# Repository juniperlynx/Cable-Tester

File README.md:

# Cable-Tester
This is a replacement PCB and software for a cheap commercial cable tester usually sold as the HL-486 (though there are other model numbers, mine is ST-M810).
It improves on the original design by adding beefier drive circuitry and a proper voltage regulator for the microcontroller.

Schematics and PCB layouts are available for both ends. The current revision of the Gerbers is untested but only contains slight variations from the most recently ordered version. Complete BOMs for both the master and remote ends are now available for both ends along with Digikey shoping carts in .csv format. I haven't been able to find a source for the multi-LED standoffs used to space the strand indicator LEDs so I've modeled a part in OpenSCAD. The OpenSCAD source and a rendered .stl file are available but untested at this time.

The original Kicad design files are in "Kicad Files/" and the software source code in "Software/".
If you'd like to build your own use the Gerber files in "Gerbers/" and the BOMs in "BOM/" along with the standoff model in "3D Parts/STL"

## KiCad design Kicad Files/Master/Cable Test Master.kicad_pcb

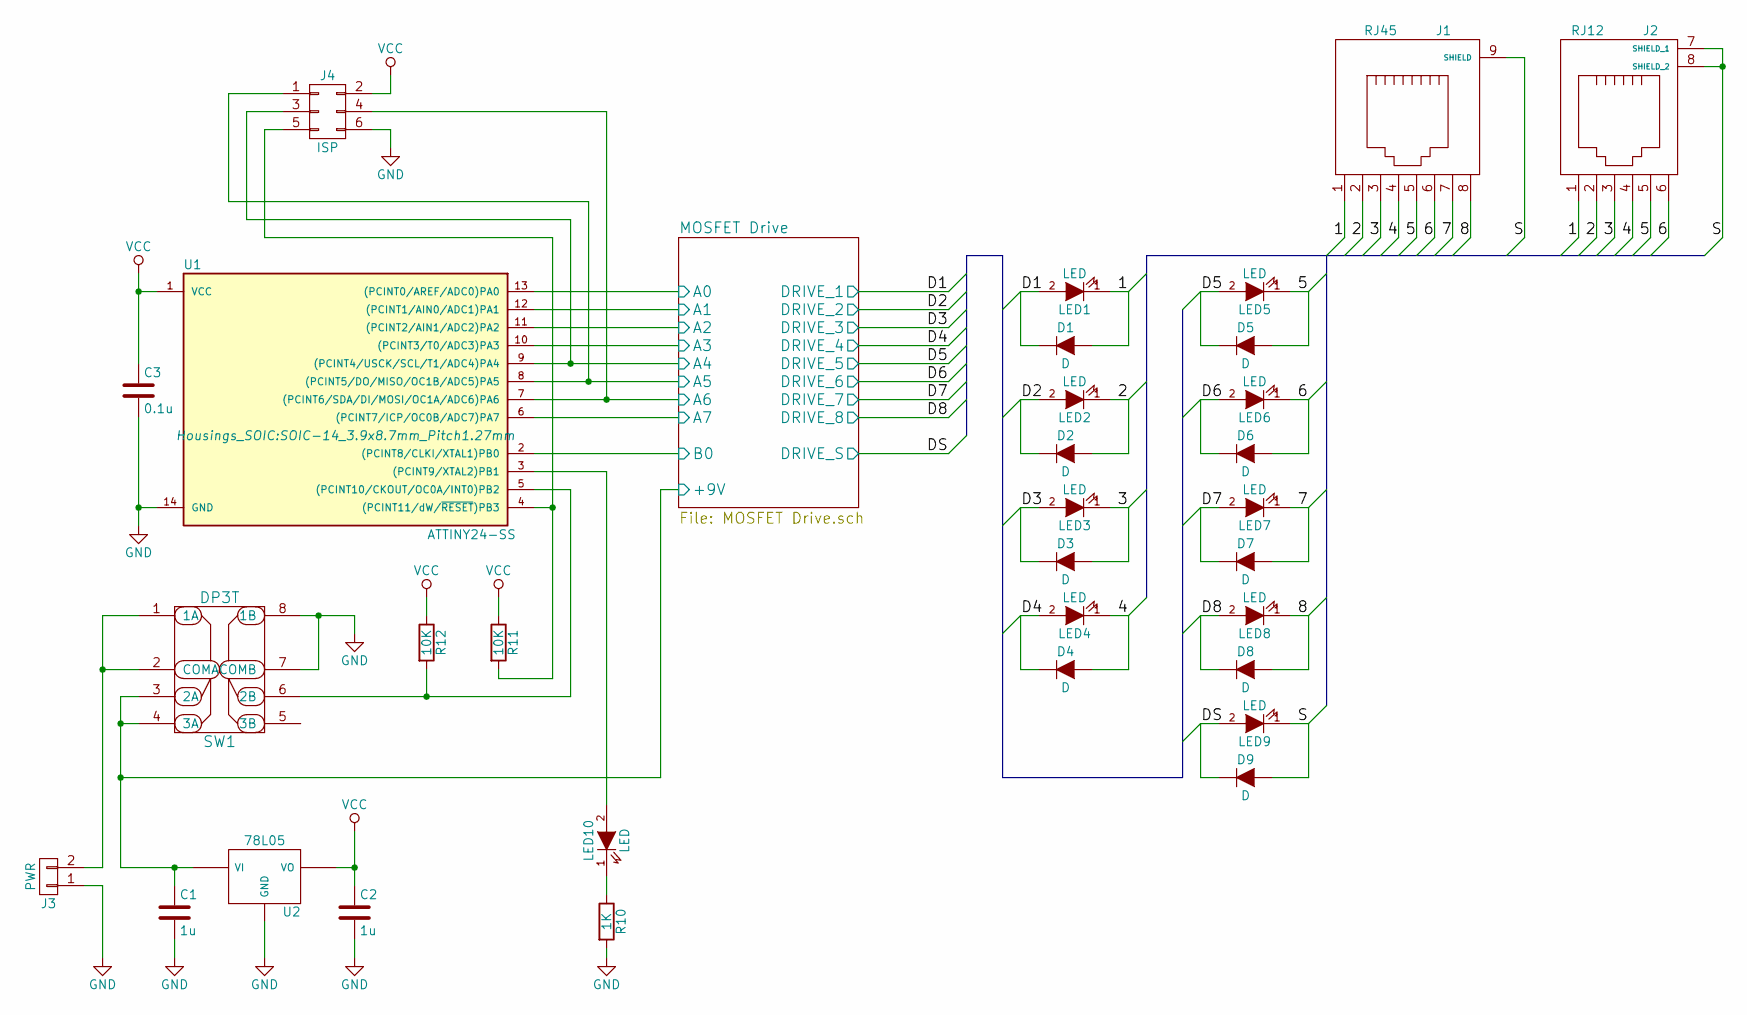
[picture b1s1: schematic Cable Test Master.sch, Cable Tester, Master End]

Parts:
C1, C2: 1u; C_0805_HandSoldering
C3: 0.1u; C_0805_HandSoldering
D1, D2, D3, D4, D5, D6, D7, D8, D9: D; SOD-123
J1: RJ45; RJ45_SHLD
J2: RJ12; RJ12_SHLD
J3: PWR; Pin_Header_Straight_1x02
J4: ISP; Pin_Header_Straight_2x03
LED1, LED2, LED3, LED4, LED5, LED6, LED7, LED8, LED9, LED10: LED; LED-3MM
R10: 1K; R_0805_HandSoldering
R11, R12: 10K; R_0805_HandSoldering
SW1: DP3T; SW_DP3T_SLIDE
U1: ATTINY24-SS; SOIC-14_3.9x8.7mm_Pitch1.27mm
U2: 78L05; 78L05_SOIC

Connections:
/1: D1.2 (A), J1.1, J2.1, LED1.1 (K)
/2: D2.2 (A), J1.2, J2.2, LED2.1 (K)
/3: D3.2 (A), J1.3, J2.3, LED3.1 (K)
/4: D4.2 (A), J1.4, J2.4, LED4.1 (K)
/5: D5.2 (A), J1.5, J2.5, LED5.1 (K)
/6: D6.2 (A), J1.6, J2.6, LED6.1 (K)
/7: D7.2 (A), J1.7, LED7.1 (K)
/8: D8.2 (A), J1.8, LED8.1 (K)
/MOSFET Drive/+9V: C1.1, SW1.3 (2A), SW1.4 (3A), U2.VI; also elsewhere on the board
/MOSFET Drive/A0: U1.13 ((PCINT0/AREF/ADC0)PA0); also elsewhere on the board
/MOSFET Drive/A1: U1.12 ((PCINT1/AIN0/ADC1)PA1); also elsewhere on the board
/MOSFET Drive/A2: U1.11 ((PCINT2/AIN1/ADC2)PA2); also elsewhere on the board
/MOSFET Drive/A3: U1.10 ((PCINT3/T0/ADC3)PA3); also elsewhere on the board
/MOSFET Drive/A4: J4.3, U1.9 ((PCINT4/USCK/SCL/T1/ADC4)PA4); also elsewhere on the board
/MOSFET Drive/A5: J4.1, U1.8 ((PCINT5/DO/MISO/OC1B/ADC5)PA5); also elsewhere on the board
/MOSFET Drive/A6: J4.4, U1.7 ((PCINT6/SDA/DI/MOSI/OC1A/ADC6)PA6); also elsewhere on the board
/MOSFET Drive/A7: U1.6 ((PCINT7/ICP/OC0B/ADC7)PA7); also elsewhere on the board
/MOSFET Drive/B0: U1.2 ((PCINT8/CLKI/XTAL1)PB0); also elsewhere on the board
/MOSFET Drive/DRIVE_1: D1.1 (K), LED1.2 (A); also elsewhere on the board
/MOSFET Drive/DRIVE_2: D2.1 (K), LED2.2 (A); also elsewhere on the board
/MOSFET Drive/DRIVE_3: D3.1 (K), LED3.2 (A); also elsewhere on the board
/MOSFET Drive/DRIVE_4: D4.1 (K), LED4.2 (A); also elsewhere on the board
/MOSFET Drive/DRIVE_5: D5.1 (K), LED5.2 (A); also elsewhere on the board
/MOSFET Drive/DRIVE_6: D6.1 (K), LED6.2 (A); also elsewhere on the board
/MOSFET Drive/DRIVE_7: D7.1 (K), LED7.2 (A); also elsewhere on the board
/MOSFET Drive/DRIVE_8: D8.1 (K), LED8.2 (A); also elsewhere on the board
/MOSFET Drive/DRIVE_S: D9.1 (K), LED9.2 (A); also elsewhere on the board
/S: D9.2 (A), J1.9 (SHIELD), J2.7 (SHIELD_1), J2.8 (SHIELD_2), LED9.1 (K)
GND: C1.2, C2.2, C3.2, J3.1, J4.6, R10.2, SW1.7 (COMB), SW1.8 (1B), U1.14 (GND), U2.GND; also elsewhere on the board
unnamed: J3.2, SW1.1 (1A), SW1.2 (COMA)
unnamed: J4.5, R11.2, U1.4 ((PCINT11/dW/~RESET~)PB3)
unnamed: LED10.1 (K), R10.1
unnamed: LED10.2 (A), U1.3 ((PCINT9/XTAL2)PB1)
unnamed: R12.2, SW1.6 (2B), U1.5 ((PCINT10/CKOUT/OC0A/INT0)PB2)
VCC: C2.1, C3.1, J4.2, R11.1, R12.1, U1.1 (VCC), U2.VO

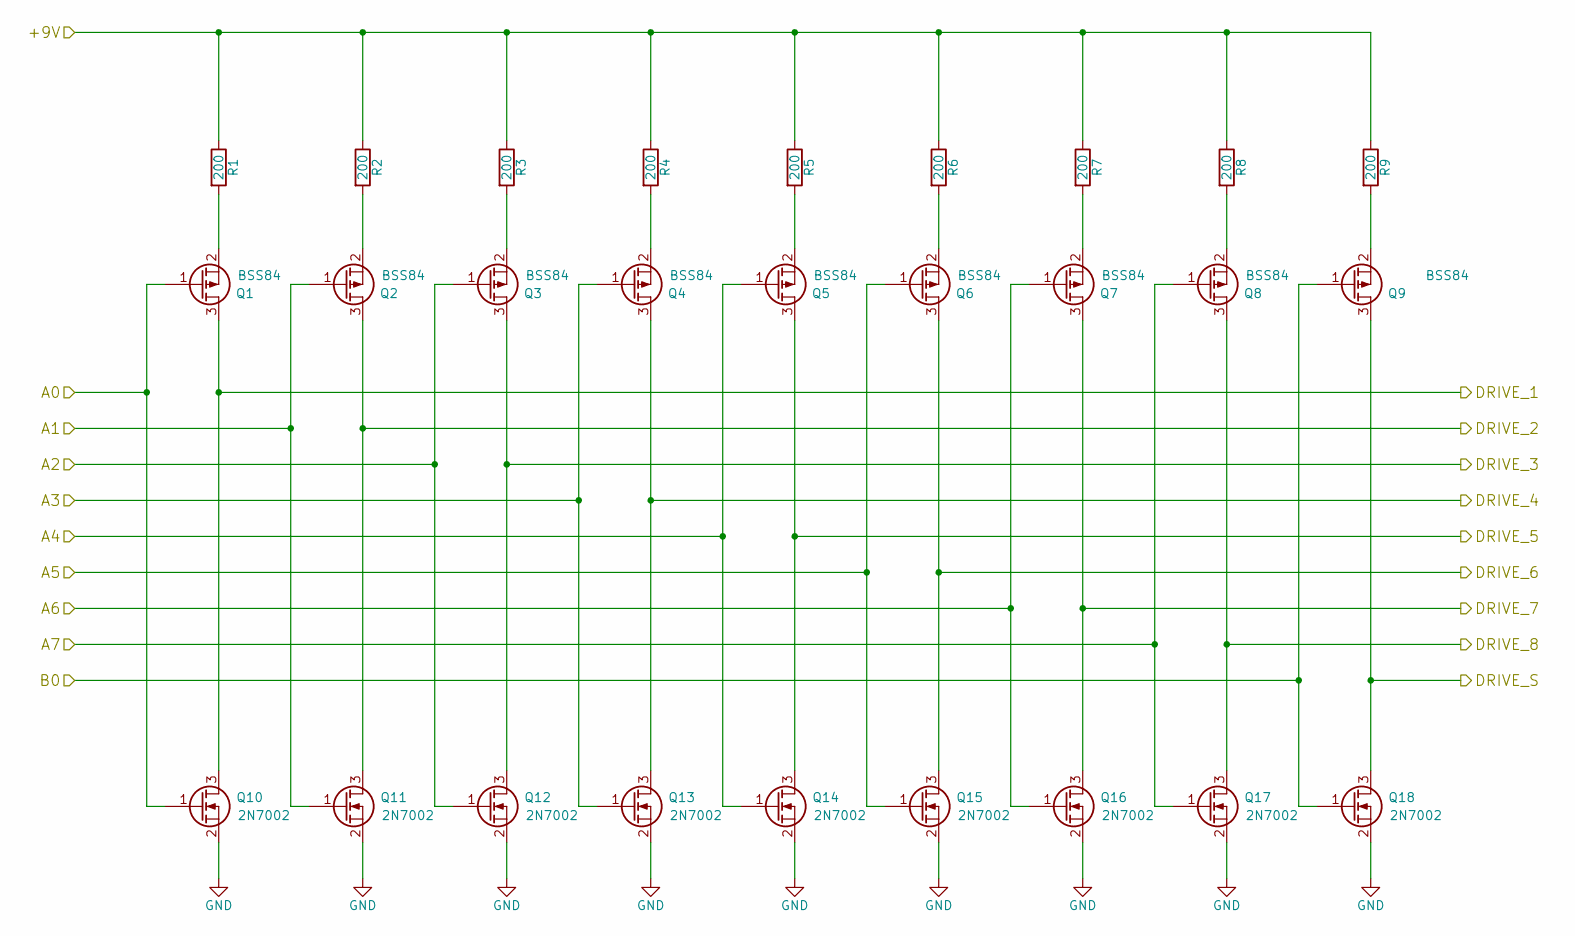
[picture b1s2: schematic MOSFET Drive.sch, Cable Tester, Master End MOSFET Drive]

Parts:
Q1, Q2, Q3, Q4, Q5, Q6, Q7, Q8, Q9: BSS84; SOT-23_Handsoldering
Q10, Q11, Q12, Q13, Q14, Q15, Q16, Q17, Q18: 2N7002; SOT-23_Handsoldering
R1, R2, R3, R4, R5, R6, R7, R8, R9: 200; R_0805_HandSoldering

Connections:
/MOSFET Drive/+9V: R1.1, R2.1, R3.1, R4.1, R5.1, R6.1, R7.1, R8.1, R9.1; also elsewhere on the board
/MOSFET Drive/A0: Q1.1 (G), Q10.1 (G); also elsewhere on the board
/MOSFET Drive/A1: Q2.1 (G), Q11.1 (G); also elsewhere on the board
/MOSFET Drive/A2: Q3.1 (G), Q12.1 (G); also elsewhere on the board
/MOSFET Drive/A3: Q4.1 (G), Q13.1 (G); also elsewhere on the board
/MOSFET Drive/A4: Q5.1 (G), Q14.1 (G); also elsewhere on the board
/MOSFET Drive/A5: Q6.1 (G), Q15.1 (G); also elsewhere on the board
/MOSFET Drive/A6: Q7.1 (G), Q16.1 (G); also elsewhere on the board
/MOSFET Drive/A7: Q8.1 (G), Q17.1 (G); also elsewhere on the board
/MOSFET Drive/B0: Q9.1 (G), Q18.1 (G); also elsewhere on the board
/MOSFET Drive/DRIVE_1: Q1.3 (D), Q10.3 (D); also elsewhere on the board
/MOSFET Drive/DRIVE_2: Q2.3 (D), Q11.3 (D); also elsewhere on the board
/MOSFET Drive/DRIVE_3: Q3.3 (D), Q12.3 (D); also elsewhere on the board
/MOSFET Drive/DRIVE_4: Q4.3 (D), Q13.3 (D); also elsewhere on the board
/MOSFET Drive/DRIVE_5: Q5.3 (D), Q14.3 (D); also elsewhere on the board
/MOSFET Drive/DRIVE_6: Q6.3 (D), Q15.3 (D); also elsewhere on the board
/MOSFET Drive/DRIVE_7: Q7.3 (D), Q16.3 (D); also elsewhere on the board
/MOSFET Drive/DRIVE_8: Q8.3 (D), Q17.3 (D); also elsewhere on the board
/MOSFET Drive/DRIVE_S: Q9.3 (D), Q18.3 (D); also elsewhere on the board
GND: Q10.2 (S), Q11.2 (S), Q12.2 (S), Q13.2 (S), Q14.2 (S), Q15.2 (S), Q16.2 (S), Q17.2 (S), Q18.2 (S); also elsewhere on the board
unnamed: Q1.2 (S), R1.2
unnamed: Q2.2 (S), R2.2
unnamed: Q3.2 (S), R3.2
unnamed: Q4.2 (S), R4.2
unnamed: Q5.2 (S), R5.2
unnamed: Q6.2 (S), R6.2
unnamed: Q7.2 (S), R7.2
unnamed: Q8.2 (S), R8.2
unnamed: Q9.2 (S), R9.2

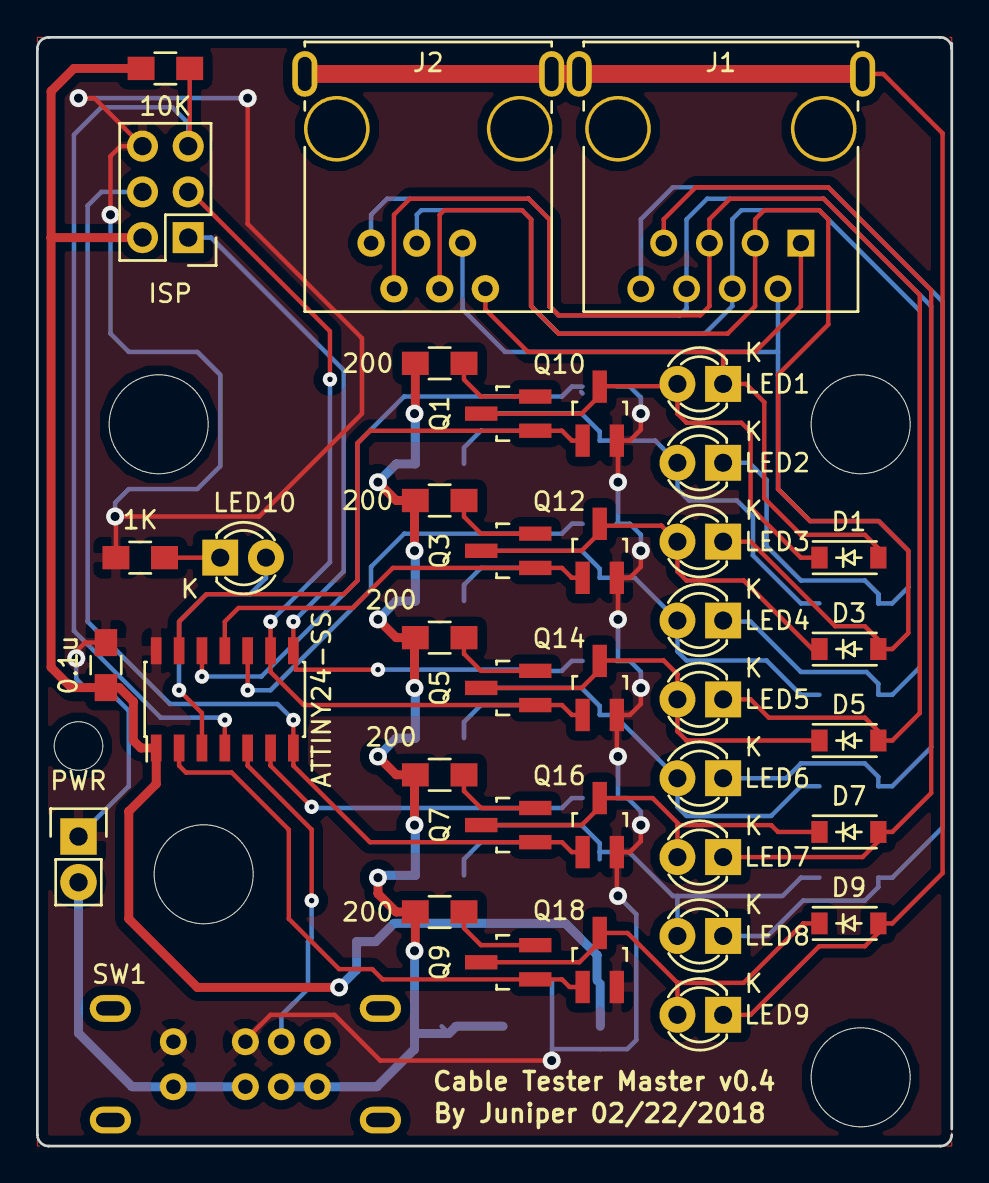
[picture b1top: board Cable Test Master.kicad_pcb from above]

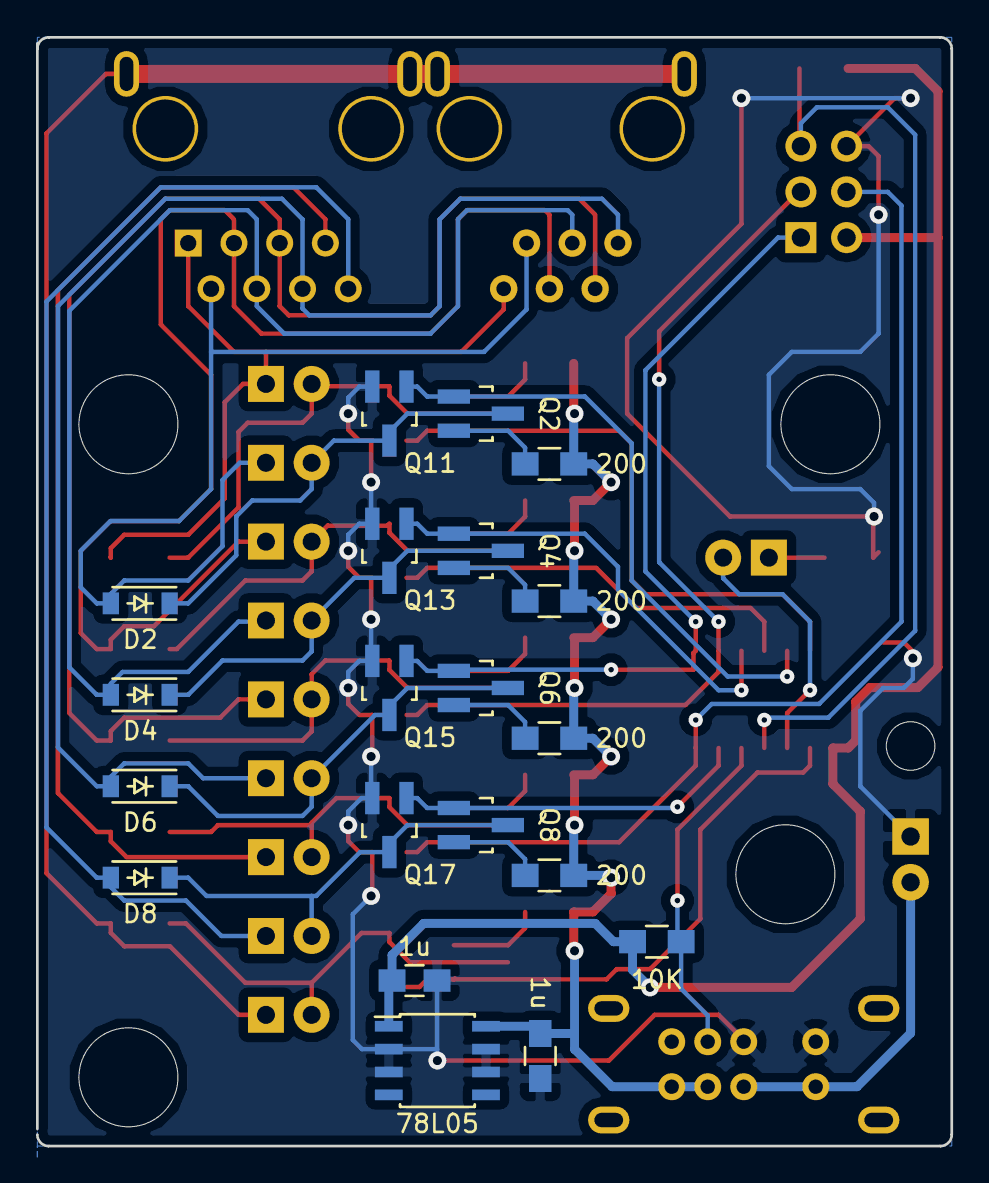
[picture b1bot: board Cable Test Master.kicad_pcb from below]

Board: 2 copper layers, 50.8 x 61.6 mm, 59 parts (20 on the bottom side), 44 nets.

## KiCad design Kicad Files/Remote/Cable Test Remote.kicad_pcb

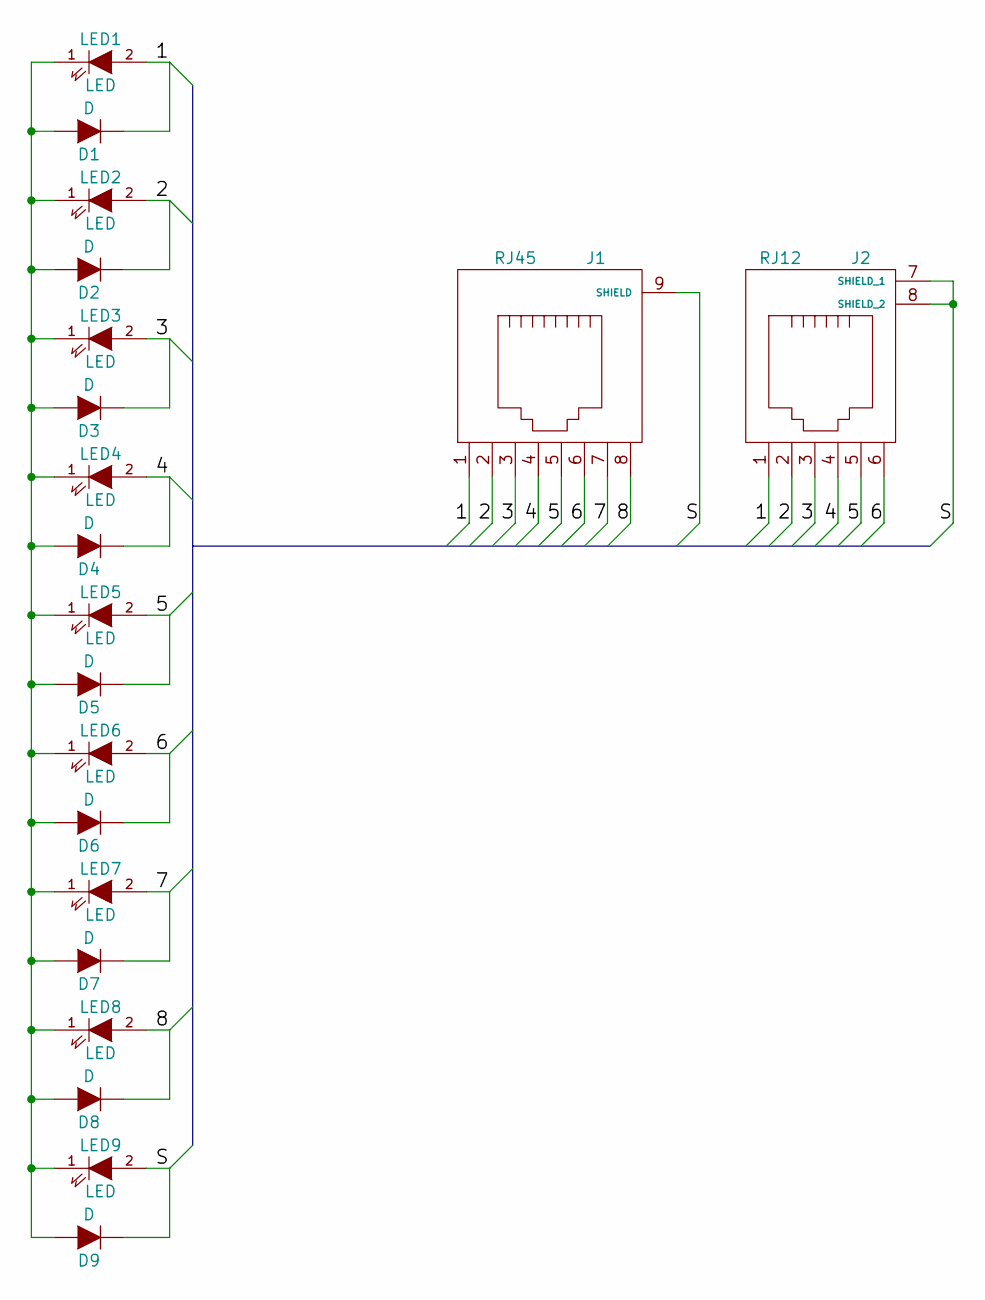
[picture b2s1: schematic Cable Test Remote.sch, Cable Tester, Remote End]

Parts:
D1, D2, D3, D4, D5, D6, D7, D8, D9: D; SOD-123
J1: RJ45; RJ45_SHLD
J2: RJ12; RJ12_SHLD
LED1, LED2, LED3, LED4, LED5, LED6, LED7, LED8, LED9: LED; LED-3MM

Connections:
/1: D1.1 (K), J1.1, J2.1, LED1.2 (A)
/2: D2.1 (K), J1.2, J2.2, LED2.2 (A)
/3: D3.1 (K), J1.3, J2.3, LED3.2 (A)
/4: D4.1 (K), J1.4, J2.4, LED4.2 (A)
/5: D5.1 (K), J1.5, J2.5, LED5.2 (A)
/6: D6.1 (K), J1.6, J2.6, LED6.2 (A)
/7: D7.1 (K), J1.7, LED7.2 (A)
/8: D8.1 (K), J1.8, LED8.2 (A)
/S: D9.1 (K), J1.9 (SHIELD), J2.7 (SHIELD_1), J2.8 (SHIELD_2), LED9.2 (A)
unnamed: D1.2 (A), D2.2 (A), D3.2 (A), D4.2 (A), D5.2 (A), D6.2 (A), D7.2 (A), D8.2 (A), D9.2 (A), LED1.1 (K), LED2.1 (K), LED3.1 (K), LED4.1 (K), LED5.1 (K), LED6.1 (K), LED7.1 (K), LED8.1 (K), LED9.1 (K)

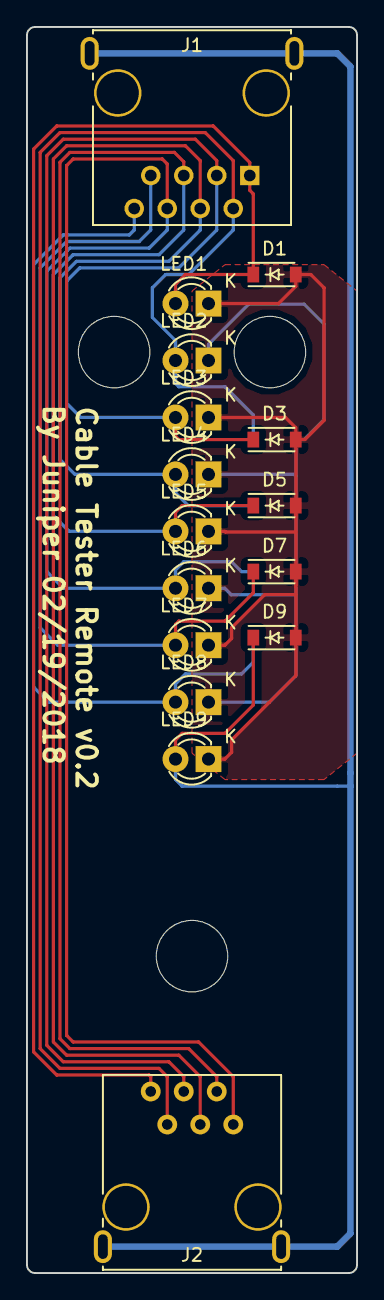
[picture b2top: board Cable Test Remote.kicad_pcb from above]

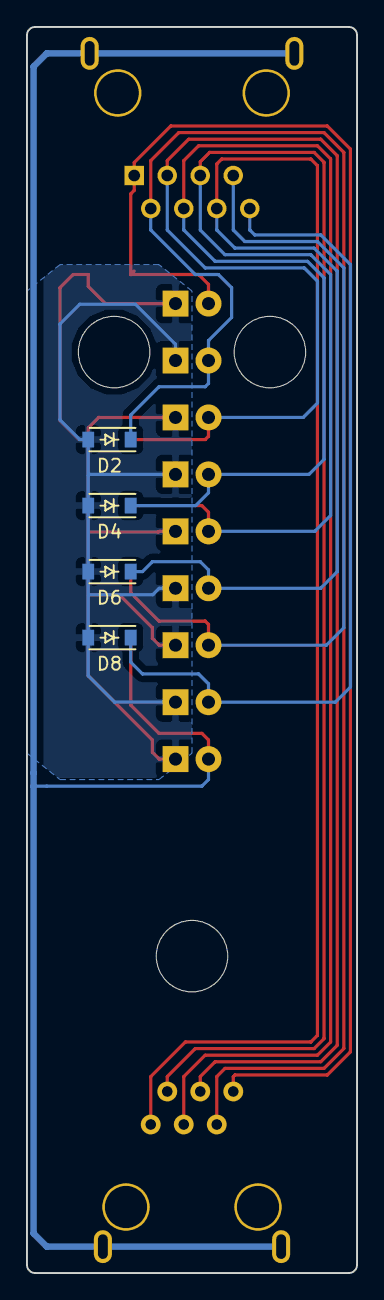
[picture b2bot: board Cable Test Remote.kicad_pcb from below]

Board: 2 copper layers, 25.4 x 95.9 mm, 20 parts (4 on the bottom side), 10 nets.

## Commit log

2018-02-03 Remove unnecessary files
2018-02-03 Cleanup additional files
2018-02-03 Change Folder Structure
2018-02-03 Add license
2018-02-04 Add BOM
2018-02-10 Fix mounting holes and RJ12 footprint
2018-02-10 Update Gerbers to reflect fixes
2018-02-11 Fix P-channel MOSFET wiring and software output levels
2018-02-16 Update license text
2018-02-16 Improve fit and finish issues
2018-02-16 Begin PCB layout
2018-02-17 Update Component Positioning on Master PCB
    Updates the positioning of components to fix positioning issues introduced
    by the earlier shortening of the board to improve fit.
2018-02-17 Perform initial trace routing for remote end PCB
    Adds traces to PCB design for the remote end of the cable tester.
2018-02-20 Adjust trace width and add text to remote end PCB
2018-02-23 Change R1-R9 to 100 ohm
2018-02-23 Update BOM for master end
2018-02-23 Generate initial remote end BOM
2018-02-24 Generate Gerbers for remote end
2018-02-24 Fix revision printing on PCB
2018-03-11 Change SW2 reference to SW1
2018-03-11 Change current limiting resistors to 200 Ohm
    The 100 Ohm resistors worked but the LEDs burn rather bright. Increasing resistance to be easier on eyes. Also changed BOM to match.
2018-03-11 Shorten Remote board to better fit case
2018-03-11 Update Gerbers to reflect changes
2018-03-18 Fix small measurement error in RJ-12 Footprint
2018-03-18 Fix small measurement error in RJ-45 Footprint
2018-03-19 Cleanup and add info to BOMs
2018-03-19 Fix footprint issues in Gerbers
2018-03-19 Added Digikey carts to BOM
2018-03-19 Add 9V battery clip to Digikey Cart
2018-03-23 Add 3d files for multi-LED standoff
2018-03-23 Bring README.md up to date with status
